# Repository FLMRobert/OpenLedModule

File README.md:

# OpenLedModule
OpenLedModule - an Open Hardware LED module project

The OpenLedModule project provides Open Hardware LED modules for everyone! 

With OpenLedModule, you can easily build your own lighting fixture - just follow these steps:

***

**Step 1**: Choose a basic LED lamp model that fits your needs

_Example_: choose [40FLATLED](https://github.com/FLMRobert/OpenLedModule/wiki/Lamps-40FLATLED) - a ceiling lamp that is as bright as two 60W light bulbs.

***

**Step 2**: Check which LED Module is required to build the lamp model

_Example_: for lamp 40FLATLED, [Module 2](https://github.com/FLMRobert/OpenLedModule/wiki/Modules---Module-2) is required

***

**Step 3**: Order the required number of LED Modules from a PCB (circuit board) manufacturer of your choice

_Example_: [order](https://github.com/FLMRobert/OpenLedModule/wiki/Ordering-Overview) five Module 2 PCBs to build lamp 40FLATLED.

***

**Step 4**: Order the parts (LEDs, resistors and pin headers) that are required for assembling the LED module

_Example_: the [Data Sheet of Module 2](https://github.com/FLMRobert/OpenLedModule/wiki/DataSheets-Modules-Module-2) lists all parts that are required for module assembly. For Module 2 you need to order eight [OSRAM Duris E5](https://github.com/FLMRobert/OpenLedModule/wiki/LEDs-OSRAM-Duris-E5) LEDs and one 30 Ohm resistor. This totals to 40 LEDs and five resistors for the five modules of lamp 40FLATLED. In addition to that you need nine pin headers that are required for connecting the module connector cables. 

***

**Step 5**: Solder your LED modules  
If you don't have reflow soldering equipment: go to a makerspace of your choice and solder it there.
Many makerspaces own a temperature-controlle "pizza oven" for reflow soldering.
With this oven, you can finalize your OpenLedModules.

***

**Step 6**: Assemble your LED lamp  
Get all the material that is required for your lamp model.

_Example_: for lamp 40FLATLED you need a power source (constant power source), an IKEA picture frame, some lasercut parts and other mounting material and cables. See [the data sheet](https://github.com/FLMRobert/OpenLedModule/wiki/DataSheets-Lamps-40FLATLED) of lamp 40FLATLED for the complete bill of materials.

***

## Motivation

You can buy cheap LED lamps in every hardware store, but many of the lamps you get there are just cheap crap.

Commercial LED lamps tend to break down after a short time and in many cases you have to throw away the whole lamp
just because only one little part of it is broken.

The solution for this problem is: **simply build your own LED lamp!**
If a part of your self made lamp breaks down: just fix that part.

* If one LED breaks: fix the LED. 
* If the whole LED module breaks: replace it.
* If the power supply breaks: replace it.

It's easy - believe me. 
If your are not able to fix it on your own: ask a friend or go to the hackerspace around the corner.

That's what the OpenLedModule project is about: we provide basic LED lamp designs that work,
while making sure that these LED lamps can also be easily maintained.

## History

The OpenLedModule project was initiated by [blinkgestalten](http://www.blinkgestalten.de/) 

## License

The OpenLedModule project is licensed under a CC BY-SA 4.0 License.
See LicenseCC_BY-SA_4.0.txt for license details or follow [this link](https://creativecommons.org/licenses/by-sa/4.0/legalcode).

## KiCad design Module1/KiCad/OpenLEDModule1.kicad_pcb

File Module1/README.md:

# OpenLedModule Module 1

## Overview 

The idea behind Module 1 was to use it for workshops where you can learn how to build your own LED lamp
by using a reflow soldering oven. So Module 1 is a good starting point if you want to build your first LED lamp.

Of course you can also use Module 1 for building your very personal torch light if you want. 

Module 1 is designed to work with battery power (6 AA rechargeable batteries).
You need to chain Module 1 three times in order to get the correct electrical current
per LED. 

Don't use less than three modules, otherwise you will destroy the LEDs.
Don't use more than three modules, ortherwise your LEDs will remain dark.
Use three of them. Really. It's true.

## Parts

* **LED:** 4 x Osram Duris E5 GW JDSTS2.EM
* **Resistor:** 2 x 14 Ohm

## Electric Characteristics

Module 1 is designed for 

* 7,2 V (voltage of six AA rechargeable batteries)
* 720 mA (typical current of six AA rechargeable batteries)
* typical current per parallel LED: 100 - 120 mA

## Light Characteristics

* Luminous Flux per Module: 204 lm (4 LEDs)
* Luminous Flux per LED: 51 lm (@ 2,95 V / 100 mA)
 
## Module 1 Applications

* LED Hand Lamp

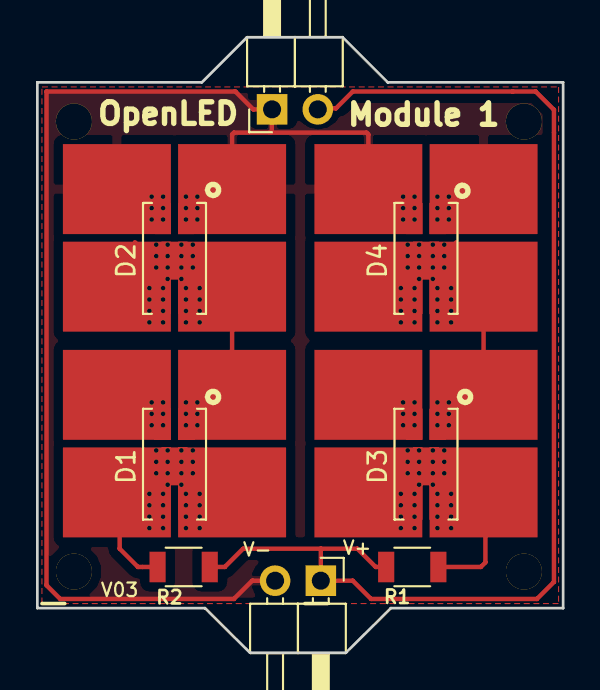
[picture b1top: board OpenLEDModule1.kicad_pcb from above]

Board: 2 copper layers, 29.2 x 34.2 mm, 9 parts (1 on the bottom side), 6 nets.

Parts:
D1, D2, D3, D4: LED; LED_OsramDURIS_E5_JDSTS2EM
P1: CONN2; Pin_Header_Angled_1x02_Pitch2.54mm
P2: CONN1; Pin_Header_Angled_1x02_Pitch2.54mm
QRCODE: LOGO; qrcode_olm_inverse2
R1, R2: 15; R_1206

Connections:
+24V: P1.2, P2.1, R1.1, R2.1
GND: D2.1, D4.1, P1.1, P2.2
unnamed: D1.1, D2.2
unnamed: D1.2, R2.2
unnamed: D3.1, D4.2
unnamed: D3.2, R1.2

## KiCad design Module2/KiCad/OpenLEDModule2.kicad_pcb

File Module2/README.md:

# OpenLedModule Module 2

## Overview 

The idea for Module 2 was to use it for standard LED lamp projects.
The module can be used for creating a LED lamp that replaces one 60 W light bulb 
(i.e. a "standard ceiling light") or to replace three 60 W light bulbs
(i.e. the "standard living room ceiling light").

Module 2 is designed to work with a constant current source of 350 mA or 700 mA.

Using a 350 mA current source corresponds ot the "one 60 W light bulb" mode:
With a 350 mA current source, you need to chain Module 2 five times 
in order to get the correct electrical current per LED.

Using a 700 mA current source corresponds ot the "three 60 W light bulbs" mode:
With a 700 mA current source, you need to chain Module 2 sevent times 
in order to get the correct electrical current per LED.

You should stick to these recommendations in order to not destroy the LEDs.

## Parts

* **LED:** 8 x Osram Duris E5 GW JDSTS2.EM
* **Resistor:** 1 x 15 Ohm

## Electric Characteristics

Module 2 is designed for operation with a 350 mA current source

* five chained modules
* 22,8 V (8 * 2,85 V) (voltage of eight serial LEDs)
* 350 mA current source
* typical current per parallel LED: 70 mA

Module 2 is designed for operation with a 700 mA current source

* seven chained modules
* 23,6 V (8 * 2,95 V) (voltage of eight serial LEDs)
* 700 mA current source
* typical current per parallel LED: 100 mA

## Light Characteristics

350 mA current source
* Total Luminous Flux: 1360 lm (5 Modules)
* Luminous Flux per Module: 272 lm (8 LEDs)
* Luminous Flux per LED: 34 lm (@ 2,85 V / 70 mA)

700 mA current source
* Total Luminous Flux: 2856 lm (7 Modules)
* Luminous Flux per Module: 408 lm (8 LEDs)
* Luminous Flux per LED: 51 lm (@ 2,95 V / 100 mA)
 
## Module 2 Applications

* Standard Ceiling Light
* Powerful Ceiling Light

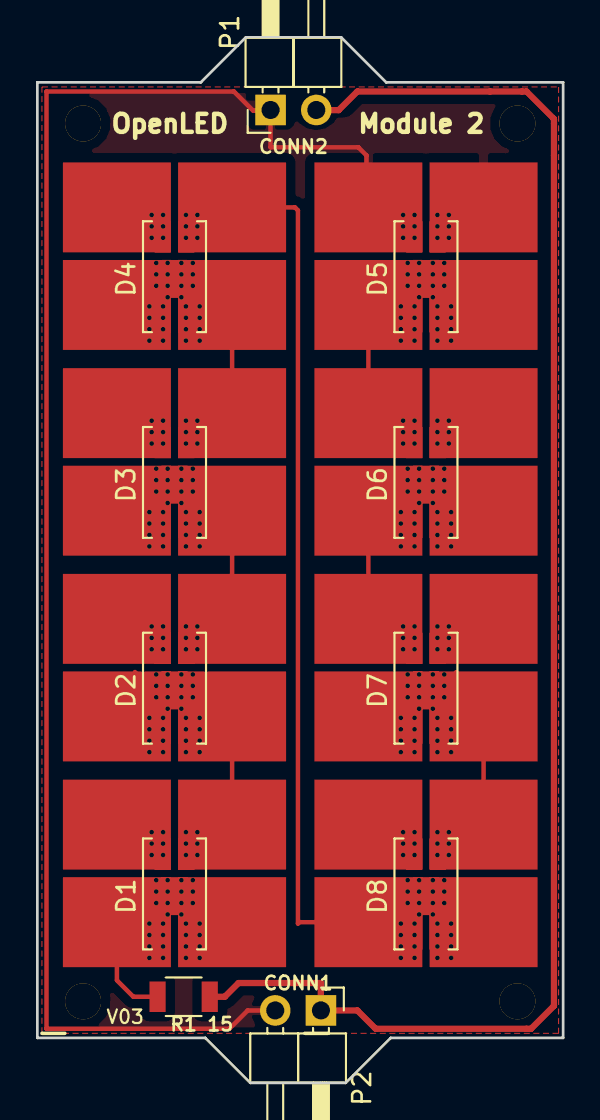
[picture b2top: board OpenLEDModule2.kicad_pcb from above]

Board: 2 copper layers, 29.2 x 58.1 mm, 11 parts (0 on the bottom side), 10 nets.

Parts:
D1, D2, D3, D4, D5, D6, D7, D8: LED; LED_OsramDURIS_E5_JDSTS2EM
P1: CONN2; Pin_Header_Angled_1x02_Pitch2.54mm
P2: CONN1; Pin_Header_Angled_1x02_Pitch2.54mm
R1: 15; R_1206

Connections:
+24V: P1.2, P2.1, R1.1
GND: D5.1, P1.1, P2.2
unnamed: D1.1, D2.2
unnamed: D1.2, R1.2
unnamed: D2.1, D3.2
unnamed: D3.1, D4.2
unnamed: D4.1, D8.2
unnamed: D5.2, D6.1
unnamed: D6.2, D7.1
unnamed: D7.2, D8.1

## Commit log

2017-04-16 Initial checkin of Module1
2017-04-16 Fixed issue with wrong size of cooling copper surfaces on back side.
2017-04-16 Initial checkin of Module 2
2017-04-16 Moved files to KiCad subfolder
2017-04-17 Added GND filling on Module 1/2. Added Gerbers.
2017-04-17 Fixed layers in pads of LED footprint.
2017-04-21 Added more project details
2017-04-21 Removed typo
2017-04-21 Created documentation of Module 1
2017-05-01 Several fixes to resolve review comments (thermal via connections, cooling pads, footprint, past and mask layers, resistors, holes, tracks)
2017-05-01 Final fixes (cleared F.Mask setting for cooling pads)
2017-06-05 Added Module01 images
2017-06-05 Added image
2017-06-05 Resized images
2017-06-05 Added images
2017-06-05 Fixed file name
2017-06-05 Added Module 2 documentation
2017-06-05 Fixed link to image
2017-06-05 Fixed image file name
2017-08-15 Updated Module 01 image. Added Module 02 images.
2017-08-15 Added images to Module 02 Readme.
2017-08-15 Updated Readme of Module 2
2017-08-15 Updated image links
2017-08-15 Beautyfied images
2017-09-01 Added lamp images
2017-09-01 Updated images
2017-09-01 Replaced image
2018-01-20 Create CONTRIBUTING
2018-01-20 Renamed file
2018-01-26 Fixed part count module 1
2018-01-27 Added Resistor Icon for BOM
2018-01-29 Added icons for 25CMLED BOM
2018-01-29 Added icons for 40FLATLED BOM
2018-01-29 Added missing 40FLATLED BOM icon
2018-01-29 Added 1MLED BOM icons
2018-01-29 Changed file type of 1MLED BOM icon
2018-01-29 Added icons for 1MLED BOM
2018-01-29 Added 25CMLED logbook images
2018-01-29 Added images for 40FLATLED Logbook
2018-01-29 Added 40FLATLED logbook images
2018-01-29 Added images for 1MLED logbook
2018-01-29 Added image for 1MLED logbook
2018-01-29 Removed file (located in wrong place)
2018-02-09 Added illustrations for Wiki
2018-02-09 Adjusted size of illustration
2018-02-09 Adjusted image size
2018-03-18 Added 25CMLED lasercuts (V6)
2018-03-24 Fixed issues #1 (header supports), #3 (four holes), #4 (polarity text). Added enhancment #8 (LED orientation marker)
2018-03-24 Fixed issue #2 (header support)
2018-03-25 25CMLED assembly instruction images
2018-03-25 Added further 25CMLED assembly instruction images
2018-03-25 Updated image 22
2018-04-01 Added Module 1 assembly instruction images
